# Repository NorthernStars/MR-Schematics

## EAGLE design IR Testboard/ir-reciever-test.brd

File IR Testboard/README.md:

IR-Testboard
============
Board to redirect IR data or/and serial Data.
Use jumpers on the board to redircet the RX or TX data to PC or an external logic.

Used for testing IR reciever.

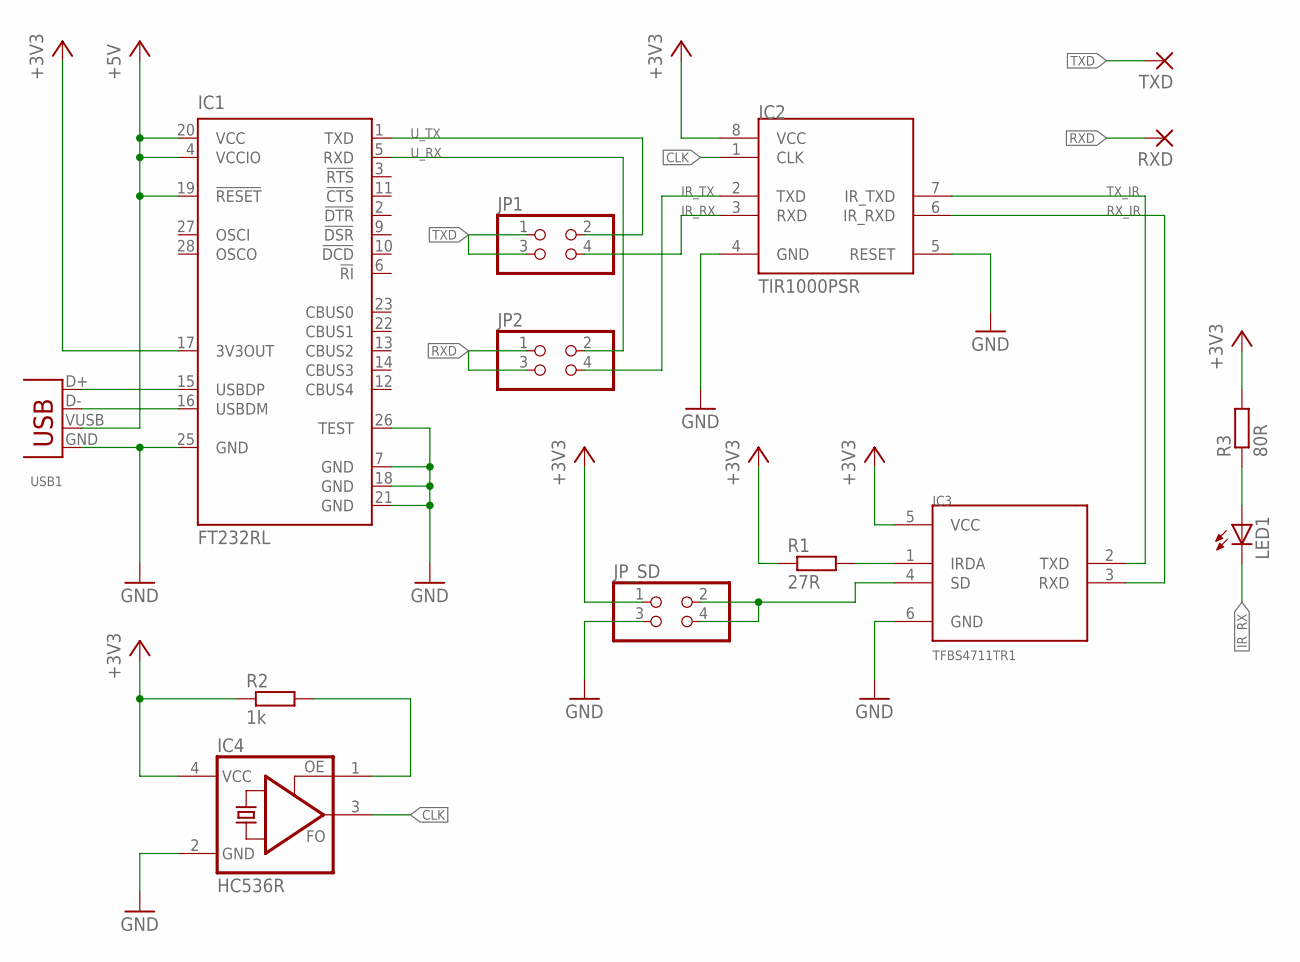
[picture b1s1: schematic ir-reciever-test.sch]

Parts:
IC1: FT232RL; SSOP28
IC2: TIR1000PSR; SO-08
IC3: TFBS4711TR1; TFBS4711
IC4: HC536R; HC536
JP1, JP2: PINHD-2X02_2.54-SMD; 2X02SMD
JP_SD: PINHD-2X02_2.54-SMD; 2X02SMD
LED1: LED3MM
R1: 27R; R1206
R2: 1k; R1206
R3: 80R; R1206
RXD: SMD5; SMD2,54-5,08
TXD: SMD5; SMD2,54-5,08
USB1: USB-B-S; USB-B-SMT

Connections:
+3V3: IC1.17 (3V3OUT), IC2.8 (VCC), IC3.5 (VCC), IC4.4 (VCC), JP_SD.1, R1.1, R2.1, R3.2
+5V: IC1.4 (VCCIO), IC1.19 (!RESET), IC1.20 (VCC), USB1.VUSB (VBUS)
CLK: IC2.1 (CLK), IC4.3 (FO)
D+: IC1.15 (USBDP), USB1.D+
D-: IC1.16 (USBDM), USB1.D-
GND: IC1.7 (GND), IC1.18 (GND), IC1.21 (GND), IC1.25 (GND), IC1.26 (TEST), IC2.4 (GND), IC2.5 (RESET), IC3.6 (GND), IC4.2 (GND), JP_SD.3, USB1.GND
IR_RX: IC2.3 (RXD), JP1.4, LED1.K (C)
IR_TX: IC2.2 (TXD), JP2.4
unnamed: LED1.A, R3.1
unnamed: IC3.1 (IRDA), R1.2
unnamed: IC3.4 (SD), JP_SD.2, JP_SD.4
unnamed: IC4.1 (OE), R2.2
RXD: JP2.1, JP2.3, RXD.1
RX_IR: IC2.6 (IR_RXD), IC3.3 (RXD)
TXD: JP1.1, JP1.3, TXD.1
TX_IR: IC2.7 (IR_TXD), IC3.2 (TXD)
U_RX: IC1.5 (RXD), JP2.2
U_TX: IC1.1 (TXD), JP1.2

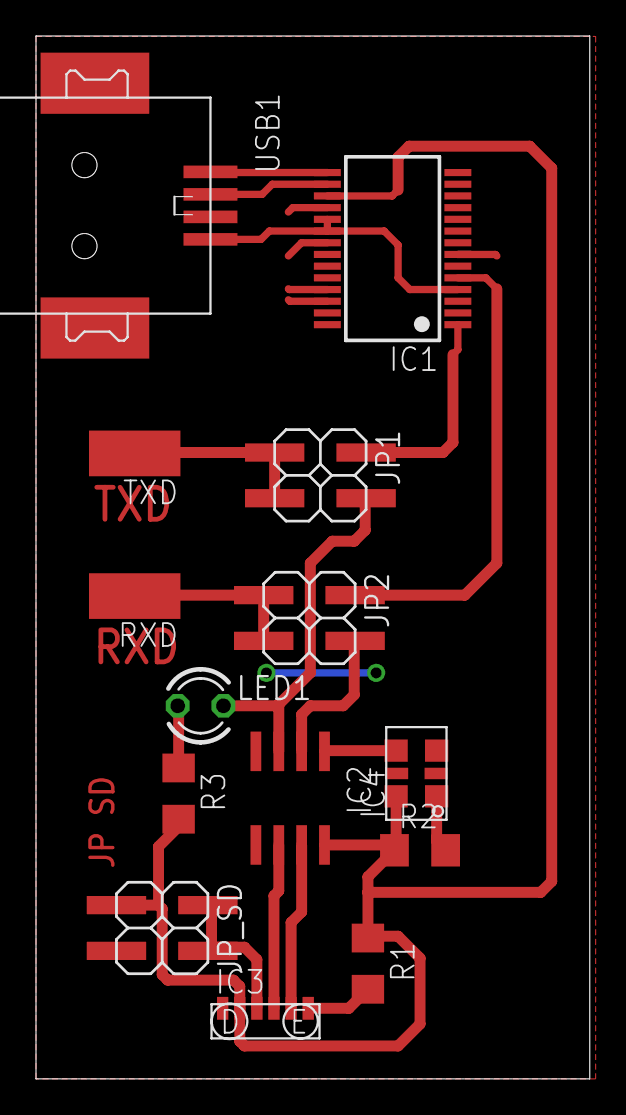
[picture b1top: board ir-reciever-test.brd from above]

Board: 2 copper layers, 30.8 x 57.9 mm, 14 parts (0 on the bottom side), 18 nets.

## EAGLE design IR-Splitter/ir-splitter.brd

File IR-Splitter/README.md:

IR-Splitter
===========
Hardware to split IR data load to seperate MOSFET channels.
Connect external power supply and IR data from IR-Transmitter to the board.
Voltage of power supply depends on you needs but test show that it should be between 5V and 12V (7.5V is recommended).

Connect IR-leds to the 10 IR-OUT pads. Try to balance the number of leds on the channels.
It's highly recommended to use a heatsink on the mosfets.

Test your installation with different intervals of load.
MOSFET's temperature should not be above 80°C!

It is possible to use this pcb as single layer board.

ATTENTION
---------
If you don't use our IR-Transmitter, take care that the IR-Splitter needs an inverted IR data input signal. So HIGH level is LOW and the other way round.

Also be aware that setting IR data input signal to LOW level will cause the leds to light up. This maybe damages them!

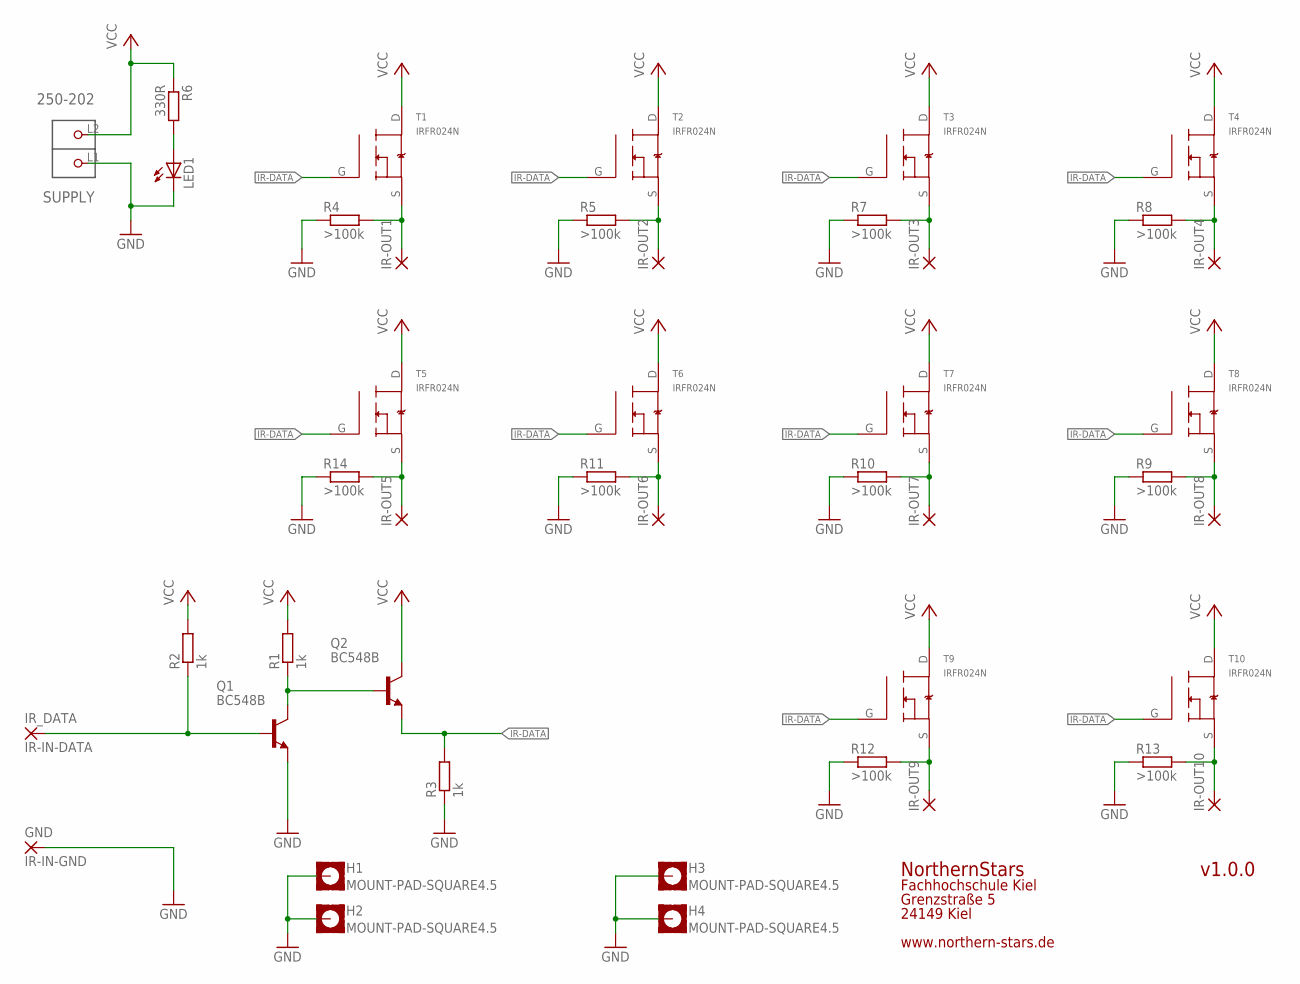
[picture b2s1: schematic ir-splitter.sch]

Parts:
GND: IR-IN-GND; 3,81/1,4
H1, H2, H3, H4: MOUNT-PAD-SQUARE4.5; 4,5-PAD-SQUARE
IR-OUT1, IR-OUT2, IR-OUT3, IR-OUT4, IR-OUT5, IR-OUT6, IR-OUT7, IR-OUT8, IR-OUT9, IR-OUT10: 3,81/1,4
IR_DATA: IR-IN-DATA; 3,81/1,4
LED1: LEDCHIPLED_1206; CHIPLED_1206
Q1, Q2: BC548B; TO92-EBC
R1, R2, R3: 1k; R1206
R4, R5, R7, R8, R9, R10, R11, R12, R13, R14: >100k; R1206
R6: 330R; R1206
SUPPLY: 250-202; P-250-202
T1, T2, T3, T4, T5, T6, T7, T8, T9, T10: IRFR024N; D-PAK

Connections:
GND: GND.1, H1.B4,5, H2.B4,5, H3.B4,5, H4.B4,5, LED1.C, Q1.E, R3.1, R4.1, R5.1, R7.1, R8.1, R9.1, R10.1, R11.1, R12.1, R13.1, R14.1, SUPPLY.L1 (P1)
IR-DATA: Q2.E, R3.2, T1.G, T2.G, T3.G, T4.G, T5.G, T6.G, T7.G, T8.G, T9.G, T10.G
unnamed: IR-OUT1.1, R4.2, T1.S
unnamed: IR-OUT2.1, R5.2, T2.S
unnamed: IR-OUT5.1, R14.2, T5.S
unnamed: IR-OUT6.1, R11.2, T6.S
unnamed: IR-OUT8.1, R9.2, T8.S
unnamed: IR-OUT7.1, R10.2, T7.S
unnamed: IR-OUT4.1, R8.2, T4.S
unnamed: IR-OUT3.1, R7.2, T3.S
unnamed: IR-OUT10.1, R13.2, T10.S
unnamed: IR-OUT9.1, R12.2, T9.S
unnamed: Q1.C, Q2.B, R1.1
unnamed: LED1.A, R6.2
unnamed: IR_DATA.1, Q1.B, R2.1
VCC: Q2.C, R1.2, R2.2, R6.1, SUPPLY.L2 (P2), T1.D, T2.D, T3.D, T4.D, T5.D, T6.D, T7.D, T8.D, T9.D, T10.D

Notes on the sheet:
NorthernStars
Fachhochschule Kiel
Grenzstraße 5
24149 Kiel
www.northern-stars.de
v1.0.0

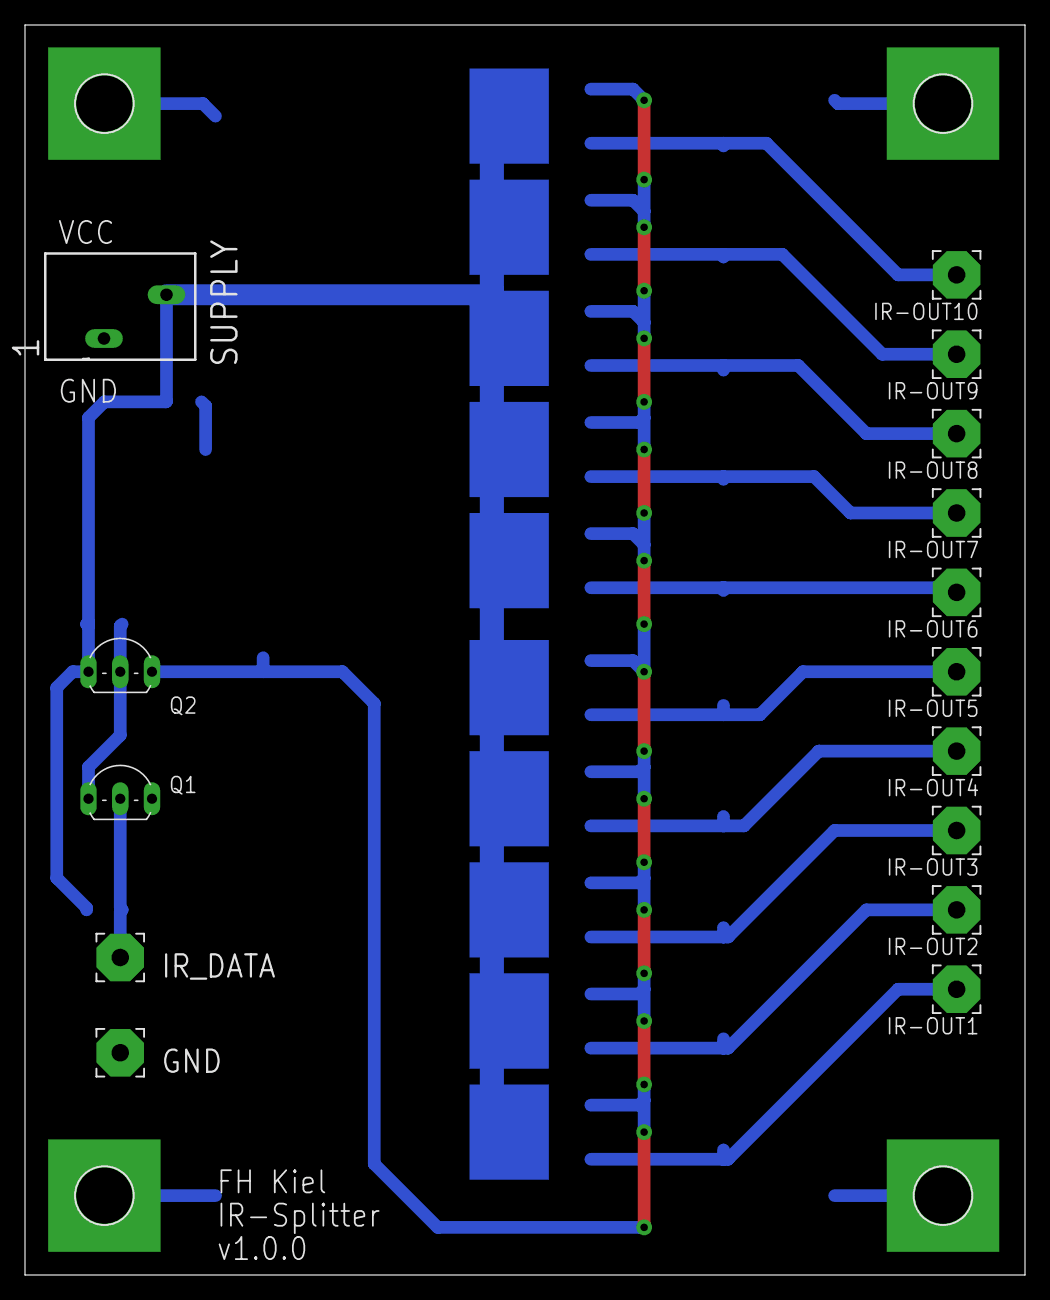
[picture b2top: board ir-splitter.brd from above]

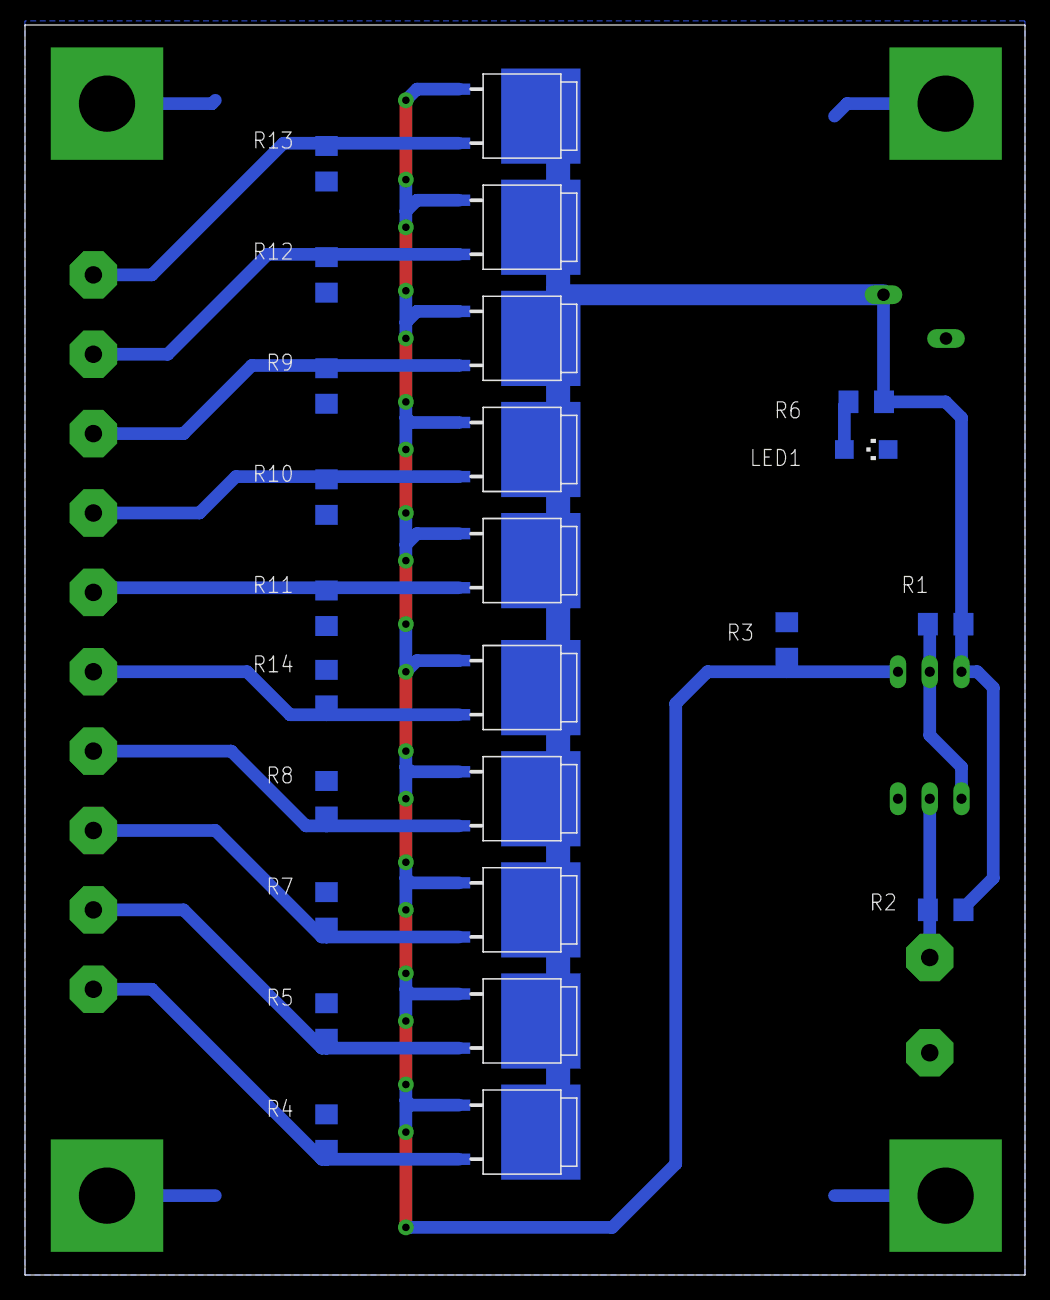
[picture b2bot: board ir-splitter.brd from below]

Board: 2 copper layers, 80.0 x 100.0 mm, 44 parts (25 on the bottom side), 16 nets.

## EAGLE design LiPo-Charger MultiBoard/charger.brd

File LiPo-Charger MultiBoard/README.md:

LiPo-Charger MultiBoard
=======================
This charger consists of several small 50x50mm board that can get connected to each other to build a charger station of your preferred size.
* The charger board includes charging circuits for charging two LiPo batteries with ~200mA/battery.
* The supply board is for connecting the charger boards to a 5V power suplly. Maximum output current ist 5.0A. It's recommended to use max. 10 charger boards at one supply board.

Order online
------------
The pcbs can be ordered very cheap from www.dirtypcbs.com
* Charger: http://dirtypcbs.com/view.php?share=21687&accesskey=b3ce18c981010ed7b3aafff49d6ba531
* Supply: http://dirtypcbs.com/view.php?share=3158&accesskey=d8e7d692d385bc674d54f8e41f2b1a86

The electronic parts should get ordered from Farnell (http://www.farnell.com) and Reichelt (https://secure.reichelt.de/index.html?LANGUAGE=EN).

The LibreOffice calculation Parts-Calculation.ods includes an adjustable list of parts to oder.

Usage
-----
To use the charger, connect at least one charger board to the supply board.
Connect the supply board with your 5V power supply. Attention: There is no protection circuit for higher voltages!
You can connect other chargers to the other sides of any charger already connected to the supply board or to the supply board itself.

I²C / TWI Bus
-------
The charger boards include a I²C (or TWI) interface to connect a microcontroller or any other logic to the robots.
For that the charger board stops the robot (depending on the correct firmware) from booting. After that you can access the robot internal hardware via I²C bus.

There will be an additional board to manage the robots in the future.

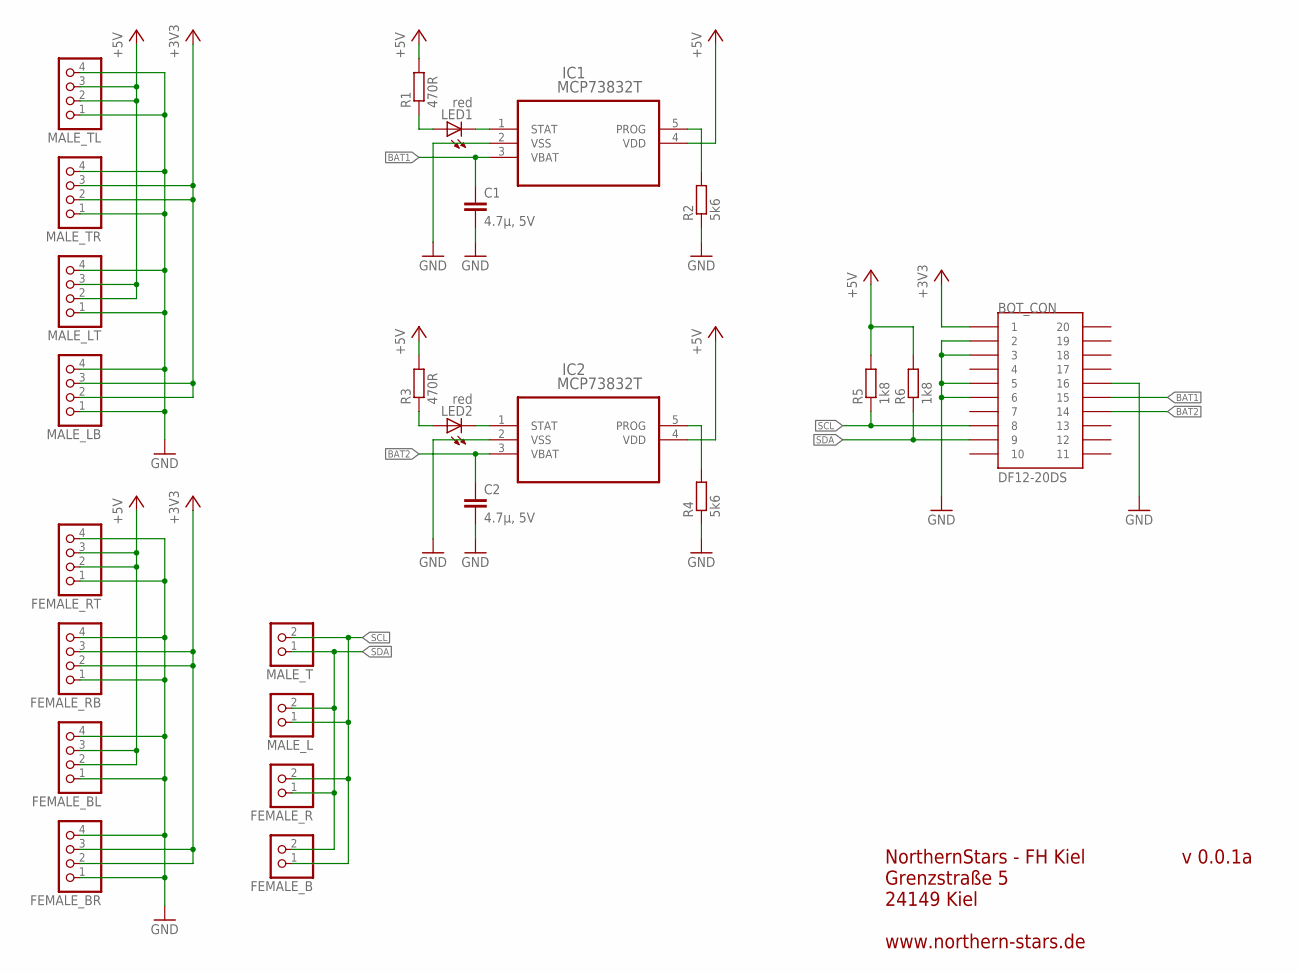
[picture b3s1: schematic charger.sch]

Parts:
BOT_CON: DF12-20DS
C1, C2: 4.7µ, 5V; C1206
FEMALE_B: PINHD-1X02_2.54-90°; 1X02/90
FEMALE_BL: PINHD-1X04_2.54-90°; 1X04/90
FEMALE_BR: PINHD-1X04_2.54-90°; 1X04/90
FEMALE_R: PINHD-1X02_2.54-90°; 1X02/90
FEMALE_RB: PINHD-1X04_2.54-90°; 1X04/90
FEMALE_RT: PINHD-1X04_2.54-90°; 1X04/90
IC1, IC2: MCP73832T; SOT95P300X145-5N
LED1, LED2: red; CHIPLED_1206
MALE_L: PINHD-1X02_2.54-90°; 1X02/90
MALE_LB: PINHD-1X04_2.54-90°; 1X04/90
MALE_LT: PINHD-1X04_2.54-90°; 1X04/90
MALE_T: PINHD-1X02_2.54-90°; 1X02/90
MALE_TL: PINHD-1X04_2.54-90°; 1X04/90
MALE_TR: PINHD-1X04_2.54-90°; 1X04/90
R1, R3: 470R; R1206
R2, R4: 5k6; R1206
R5, R6: 1k8; R1206

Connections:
+3V3: BOT_CON.1, FEMALE_BR.2, FEMALE_BR.3, FEMALE_RB.2, FEMALE_RB.3, MALE_LB.2, MALE_LB.3, MALE_TR.2, MALE_TR.3
+5V: FEMALE_BL.2, FEMALE_BL.3, FEMALE_RT.2, FEMALE_RT.3, IC1.4 (VDD), IC2.4 (VDD), MALE_LT.2, MALE_LT.3, MALE_TL.2, MALE_TL.3, R1.2, R3.2, R5.2, R6.2
BAT1: BOT_CON.15, C1.1, IC1.3 (VBAT)
BAT2: BOT_CON.14, C2.1, IC2.3 (VBAT)
GND: BOT_CON.2, BOT_CON.3, BOT_CON.5, BOT_CON.6, BOT_CON.16, C1.2, C2.2, FEMALE_BL.1, FEMALE_BL.4, FEMALE_BR.1, FEMALE_BR.4, FEMALE_RB.1, FEMALE_RB.4, FEMALE_RT.1, FEMALE_RT.4, IC1.2 (VSS), IC2.2 (VSS), MALE_LB.1, MALE_LB.4, MALE_LT.1, MALE_LT.4, MALE_TL.1, MALE_TL.4, MALE_TR.1, MALE_TR.4, R2.1, R4.1
unnamed: IC1.1 (STAT), LED1.C
unnamed: LED1.A, R1.1
unnamed: IC2.1 (STAT), LED2.C
unnamed: IC1.5 (PROG), R2.2
unnamed: LED2.A, R3.1
unnamed: IC2.5 (PROG), R4.2
SCL: BOT_CON.8, FEMALE_B.1, FEMALE_R.2, MALE_L.1, MALE_T.2, R5.1
SDA: BOT_CON.9, FEMALE_B.2, FEMALE_R.1, MALE_L.2, MALE_T.1, R6.1

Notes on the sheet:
v 0.0.1a
NorthernStars - FH Kiel Grenzstraße 5 24149 Kiel www.northern-stars.de

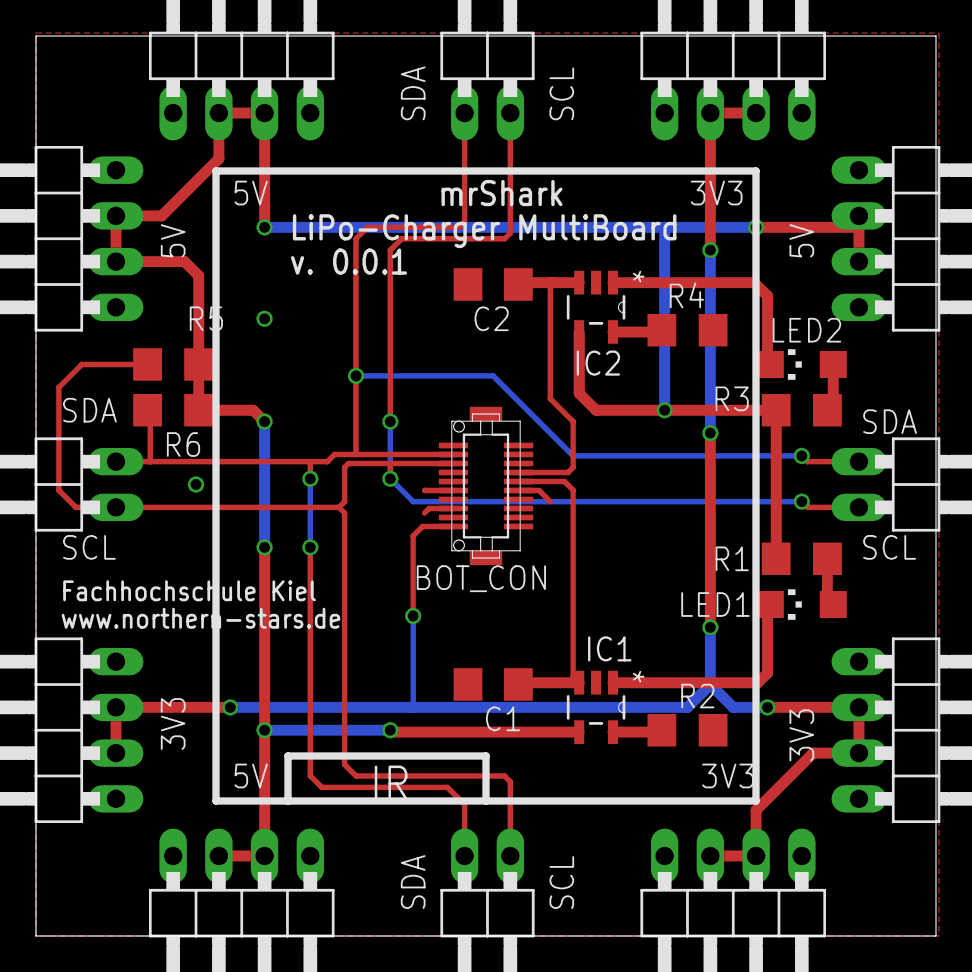
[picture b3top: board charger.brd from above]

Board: 2 copper layers, 50.0 x 50.0 mm, 25 parts (0 on the bottom side), 13 nets.

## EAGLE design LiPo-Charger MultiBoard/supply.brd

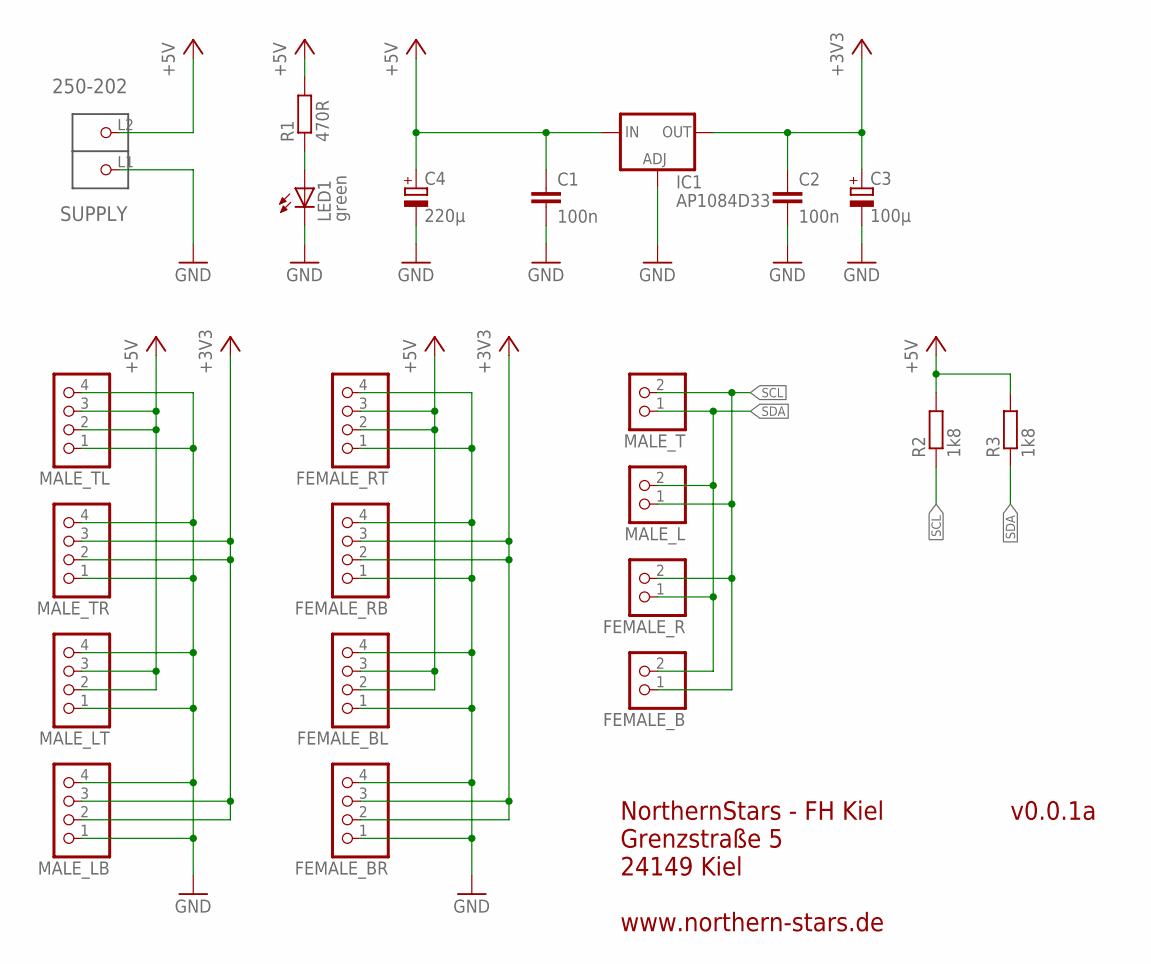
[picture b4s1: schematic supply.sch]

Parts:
C1, C2: 100n; C1206
C3: 100µ; UD-6,3X5,8_NICHICON
C4: 220µ; UD-6,3X7,7_NICHICON
FEMALE_B: PINHD-1X02_2.54-90°; 1X02/90
FEMALE_BL: PINHD-1X04_2.54-90°; 1X04/90
FEMALE_BR: PINHD-1X04_2.54-90°; 1X04/90
FEMALE_R: PINHD-1X02_2.54-90°; 1X02/90
FEMALE_RB: PINHD-1X04_2.54-90°; 1X04/90
FEMALE_RT: PINHD-1X04_2.54-90°; 1X04/90
IC1: AP1084D33; TO252
LED1: green; CHIPLED_1206
MALE_L: PINHD-1X02_2.54-90°; 1X02/90
MALE_LB: PINHD-1X04_2.54-90°; 1X04/90
MALE_LT: PINHD-1X04_2.54-90°; 1X04/90
MALE_T: PINHD-1X02_2.54-90°; 1X02/90
MALE_TL: PINHD-1X04_2.54-90°; 1X04/90
MALE_TR: PINHD-1X04_2.54-90°; 1X04/90
R1: 470R; R1206
R2, R3: 1k8; R1206
SUPPLY: 250-202; P-250-202

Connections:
+3V3: C2.1, C3.+, FEMALE_BR.2, FEMALE_BR.3, FEMALE_RB.2, FEMALE_RB.3, IC1.3 (OUT), MALE_LB.2, MALE_LB.3, MALE_TR.2, MALE_TR.3
+5V: C1.1, C4.+, FEMALE_BL.2, FEMALE_BL.3, FEMALE_RT.2, FEMALE_RT.3, IC1.2 (IN), MALE_LT.2, MALE_LT.3, MALE_TL.2, MALE_TL.3, R1.2, R2.2, R3.2, SUPPLY.L2 (P2)
GND: C1.2, C2.2, C3.-, C4.-, FEMALE_BL.1, FEMALE_BL.4, FEMALE_BR.1, FEMALE_BR.4, FEMALE_RB.1, FEMALE_RB.4, FEMALE_RT.1, FEMALE_RT.4, IC1.1 (ADJ), LED1.C, MALE_LB.1, MALE_LB.4, MALE_LT.1, MALE_LT.4, MALE_TL.1, MALE_TL.4, MALE_TR.1, MALE_TR.4, SUPPLY.L1 (P1)
unnamed: LED1.A, R1.1
SCL: FEMALE_B.1, FEMALE_R.2, MALE_L.1, MALE_T.2, R2.1
SDA: FEMALE_B.2, FEMALE_R.1, MALE_L.2, MALE_T.1, R3.1

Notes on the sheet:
v0.0.1a
NorthernStars - FH Kiel Grenzstraße 5 24149 Kiel www.northern-stars.de

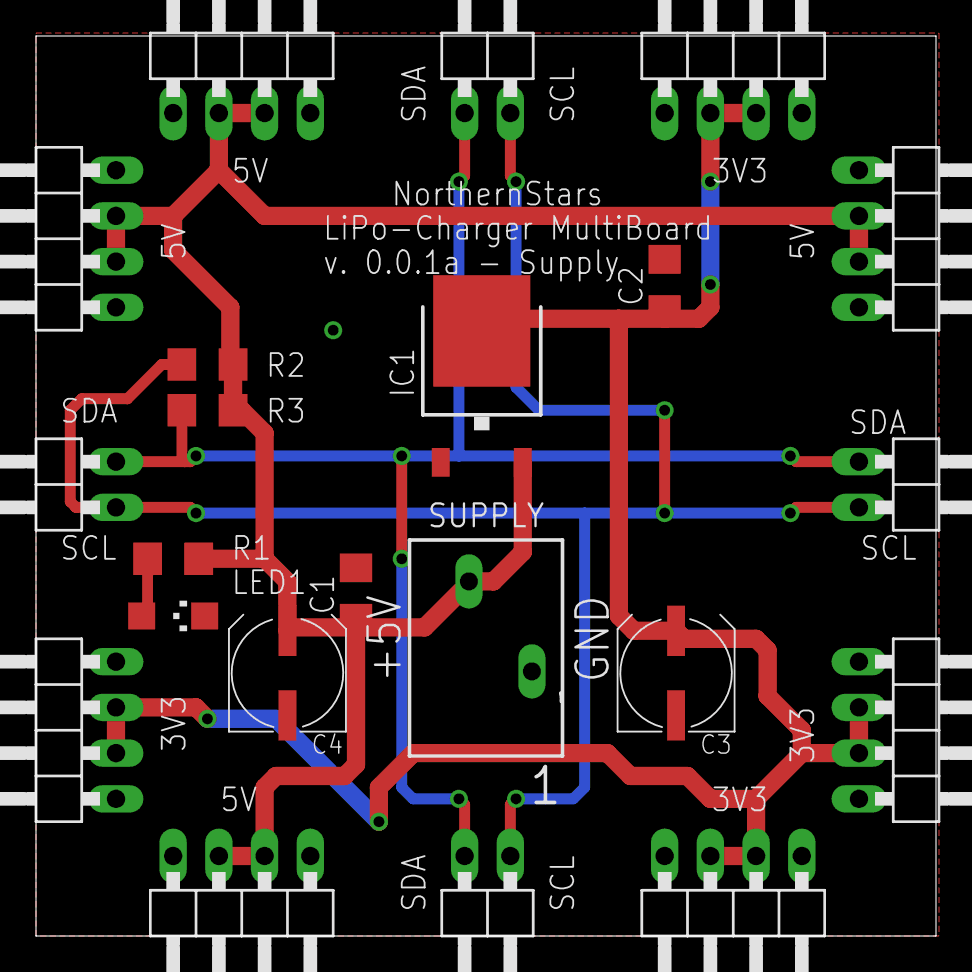
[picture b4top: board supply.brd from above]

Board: 2 copper layers, 50.0 x 50.0 mm, 22 parts (0 on the bottom side), 6 nets.

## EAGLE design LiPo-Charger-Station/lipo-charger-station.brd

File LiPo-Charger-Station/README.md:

LiPo-Charger-Station
====================

## DO NOT USE, NOT TESTED AND LAYOUT OUTDATED

This charger station includes LiPo charger circuits to charge 9 robots with 2 LiPo batterys each.
Each battery will be charged with ~500mA. The station includes a microcontroller to access the robots internal hardware.

This project currently not maintained and includes some erros. Use LiPo-Charger MutliBoard instead.

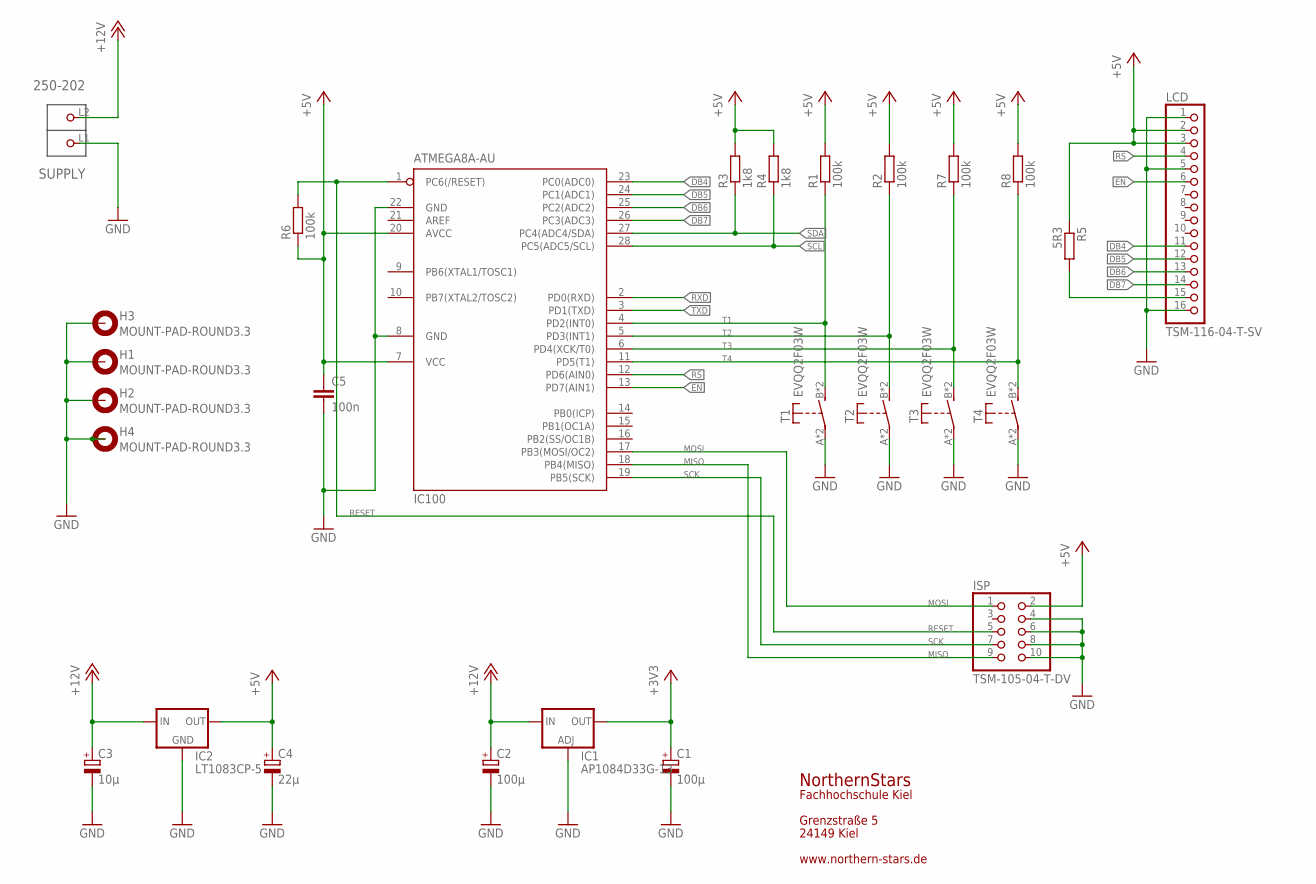
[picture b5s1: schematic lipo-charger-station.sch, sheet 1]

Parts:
C1, C2: 100µ; PANASONIC_G
C3: 10µ; PANASONIC_D
C4: 22µ; PANASONIC_E
C5: 100n; C1206
H1, H2, H3, H4: MOUNT-PAD-ROUND3.3; 3,3-PAD
IC1: AP1084D33G-13; TO252
IC2: LT1083CP-5; TO3P
IC100: ATMEGA8A-AU; DIL28-3
ISP: TSM-105-04-T-DV; 2X05SMD
LCD: TSM-116-04-T-SV; 1X16SMD
R1, R2, R6, R7, R8: 100k; R1206
R3, R4: 1k8; R1206
R5: 5R3; R1206
SUPPLY: 250-202; P-250-202
T1, T2, T3, T4: EVQQ2F03W; SMD_TASTER_PANASONIC

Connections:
+3V3: C1.+, IC1.3 (OUT); also elsewhere on the board
+5V: C4.+, C5.1, IC2.2 (OUT), IC100.7 (VCC), IC100.20 (AVCC), ISP.2, LCD.2, LCD.3, R1.2, R2.2, R3.2, R4.2, R5.1, R6.1, R7.2, R8.2; also elsewhere on the board
+12V: C2.+, C3.+, IC1.2 (IN), IC2.3 (IN), SUPPLY.L2 (P2)
DB4: IC100.23 (PC0(ADC0)), LCD.11
DB5: IC100.24 (PC1(ADC1)), LCD.12
DB6: IC100.25 (PC2(ADC2)), LCD.13
DB7: IC100.26 (PC3(ADC3)), LCD.14
EN: IC100.13 (PD7(AIN1)), LCD.6
GND: C1.-, C2.-, C3.-, C4.-, C5.2, H1.B3,3, H2.B3,3, H3.B3,3, H4.B3,3, IC1.1 (ADJ), IC2.1 (GND), IC100.8 (GND), IC100.22 (GND), ISP.4, ISP.6, ISP.8, ISP.10, LCD.1, LCD.5, LCD.16, SUPPLY.L1 (P1), T1.A, T1.A', T2.A, T2.A', T3.A, T3.A', T4.A, T4.A'; also elsewhere on the board
LEDA: LCD.15, R5.2
MISO: IC100.18 (PB4(MISO)), ISP.9
MOSI: IC100.17 (PB3(MOSI/OC2)), ISP.1
RESET: IC100.1 (PC6(/RESET)), ISP.5, R6.2
RS: IC100.12 (PD6(AIN0)), LCD.4
RXD: IC100.2 (PD0(RXD))
SCK: IC100.19 (PB5(SCK)), ISP.7
SCL: IC100.28 (PC5(ADC5/SCL)), R4.1; also elsewhere on the board
SDA: IC100.27 (PC4(ADC4/SDA)), R3.1; also elsewhere on the board
T1: IC100.4 (PD2(INT0)), R1.1, T1.B (S), T1.B' (S)
T2: IC100.5 (PD3(INT1)), R2.1, T2.B (S), T2.B' (S)
T3: IC100.6 (PD4(XCK/T0)), R7.1, T3.B (S), T3.B' (S)
T4: IC100.11 (PD5(T1)), R8.1, T4.B (S), T4.B' (S)
TXD: IC100.3 (PD1(TXD))

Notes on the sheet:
NorthernStars
Fachhochschule Kiel
Grenzstraße 5
24149 Kiel
www.northern-stars.de

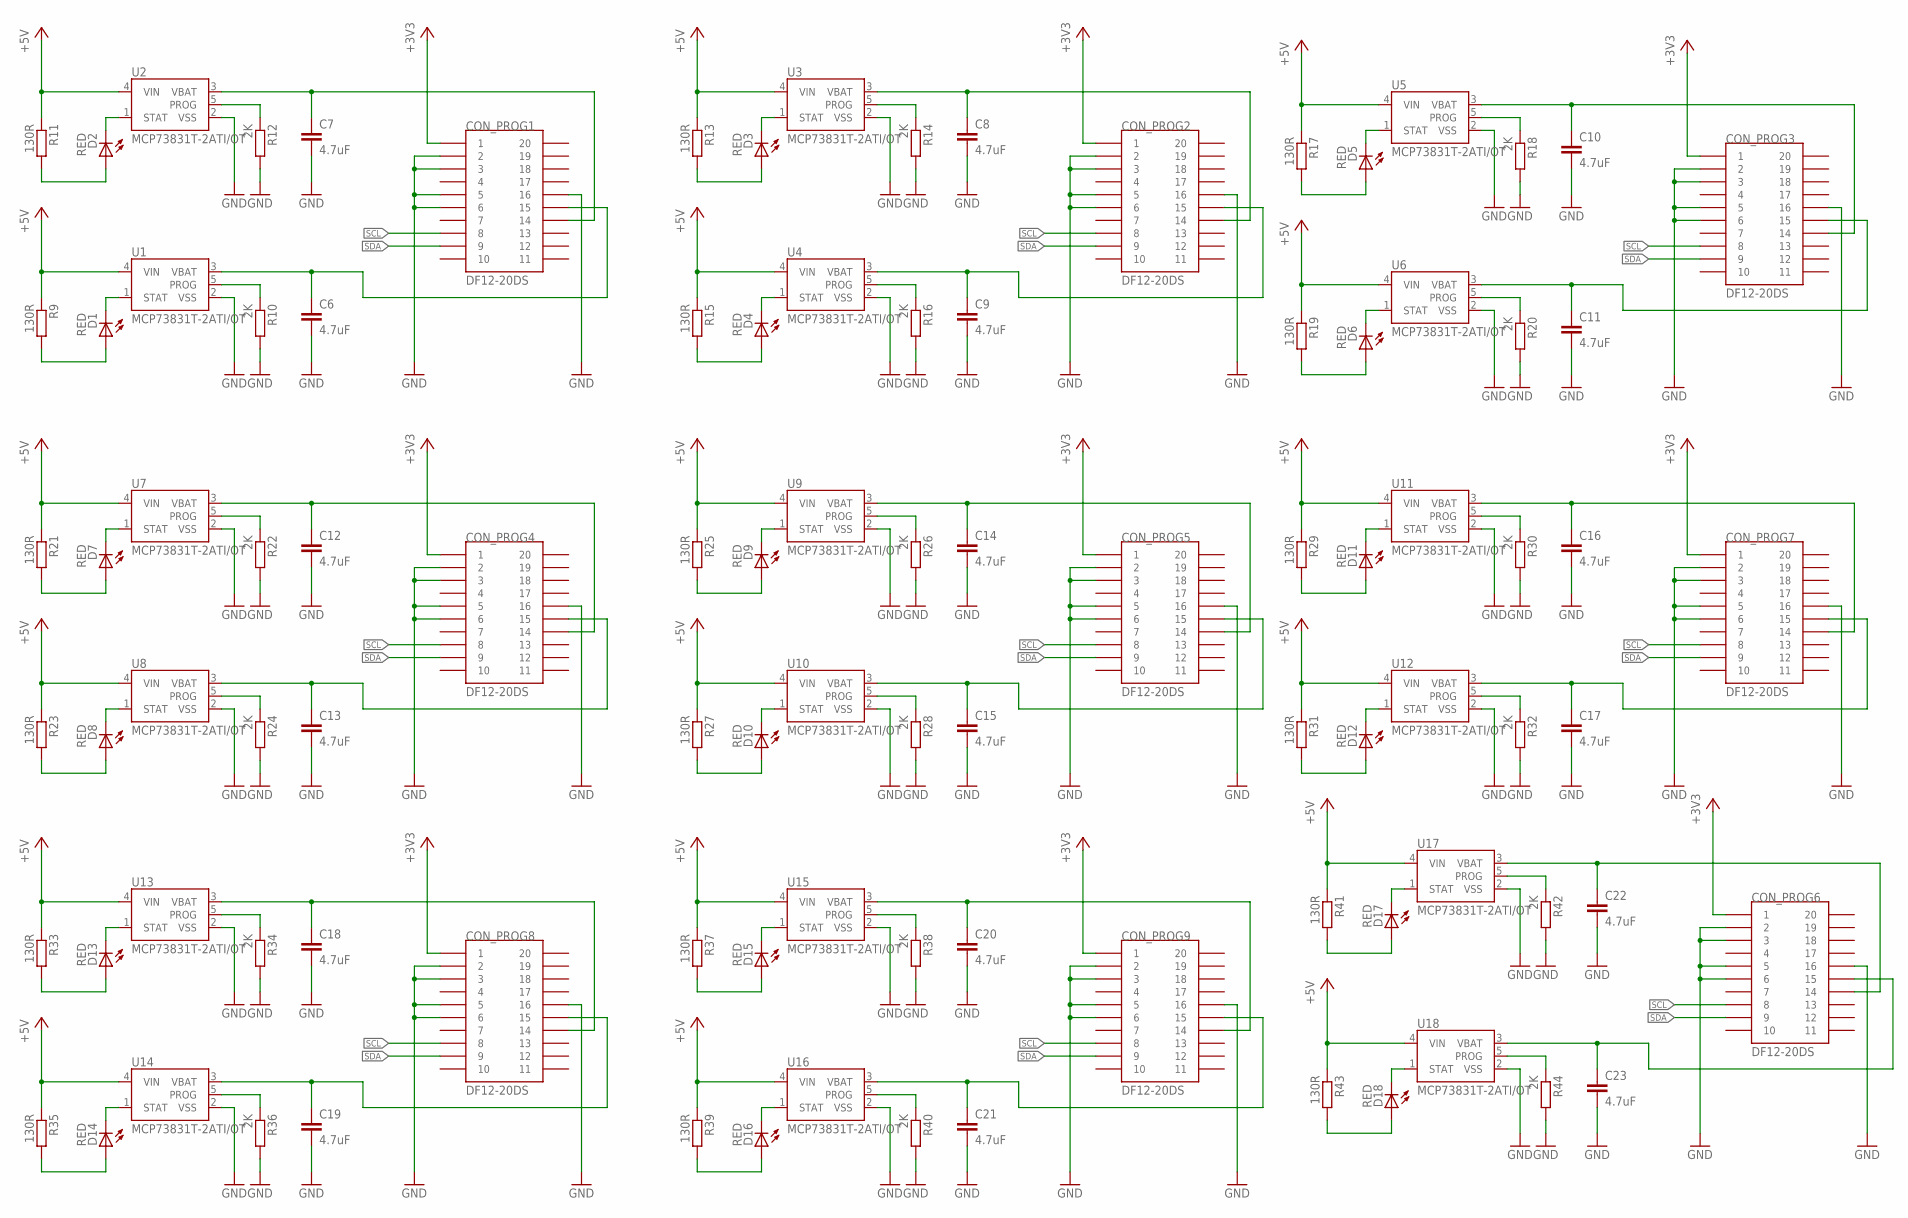
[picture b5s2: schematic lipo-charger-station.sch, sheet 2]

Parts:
C6, C7, C8, C9, C10, C11, C12, C13, C14, C15, C16, C17, C18, C19, C20, C21, C22, C23: 4.7uF; C1206
CON_PROG1, CON_PROG2, CON_PROG3, CON_PROG4, CON_PROG5, CON_PROG6, CON_PROG7, CON_PROG8, CON_PROG9: DF12-20DS
D1, D2, D3, D4, D5, D6, D7, D8, D9, D10, D11, D12, D13, D14, D15, D16, D17, D18: RED; CHIPLED_1206
R9, R11, R13, R15, R17, R19, R21, R23, R25, R27, R29, R31, R33, R35, R37, R39, R41, R43: 130R; R1206
R10, R12, R14, R16, R18, R20, R22, R24, R26, R28, R30, R32, R34, R36, R38, R40, R42, R44: 2K; R1206
U1, U2, U3, U4, U5, U6, U7, U8, U9, U10, U11, U12, U13, U14, U15, U16, U17, U18: MCP73831T-2ATI/OT; SOT23-5

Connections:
+3V3: CON_PROG1.1, CON_PROG2.1, CON_PROG3.1, CON_PROG4.1, CON_PROG5.1, CON_PROG6.1, CON_PROG7.1, CON_PROG8.1, CON_PROG9.1; also elsewhere on the board
+5V: R9.1, R11.1, R13.1, R15.1, R17.1, R19.1, R21.1, R23.1, R25.1, R27.1, R29.1, R31.1, R33.1, R35.1, R37.1, R39.1, R41.1, R43.1, U1.4 (VIN), U2.4 (VIN), U3.4 (VIN), U4.4 (VIN), U5.4 (VIN), U6.4 (VIN), U7.4 (VIN), U8.4 (VIN), U9.4 (VIN), U10.4 (VIN), U11.4 (VIN), U12.4 (VIN), U13.4 (VIN), U14.4 (VIN), U15.4 (VIN), U16.4 (VIN), U17.4 (VIN), U18.4 (VIN); also elsewhere on the board
B1_BAT1+: C7.1, CON_PROG1.14, U2.3 (VBAT)
B1_BAT1+1: C8.1, CON_PROG2.14, U3.3 (VBAT)
B1_BAT1+3: C10.1, CON_PROG3.14, U5.3 (VBAT)
B1_BAT1+4: C12.1, CON_PROG4.14, U7.3 (VBAT)
B1_BAT1+5: C16.1, CON_PROG7.14, U11.3 (VBAT)
B1_BAT1+6: C14.1, CON_PROG5.14, U9.3 (VBAT)
B1_BAT1+7: C22.1, CON_PROG6.14, U17.3 (VBAT)
B1_BAT1+9: C18.1, CON_PROG8.14, U13.3 (VBAT)
B1_BAT1+10: C20.1, CON_PROG9.14, U15.3 (VBAT)
B1_BAT2+: C6.1, CON_PROG1.15, U1.3 (VBAT)
B1_BAT2+1: C9.1, CON_PROG2.15, U4.3 (VBAT)
B1_BAT2+2: C11.1, CON_PROG3.15, U6.3 (VBAT)
B1_BAT2+3: C13.1, CON_PROG4.15, U8.3 (VBAT)
B1_BAT2+4: C15.1, CON_PROG5.15, U10.3 (VBAT)
B1_BAT2+5: C17.1, CON_PROG7.15, U12.3 (VBAT)
B1_BAT2+6: C19.1, CON_PROG8.15, U14.3 (VBAT)
B1_BAT2+7: C21.1, CON_PROG9.15, U16.3 (VBAT)
B1_BAT2+8: C23.1, CON_PROG6.15, U18.3 (VBAT)
GND: C6.2, C7.2, C8.2, C9.2, C10.2, C11.2, C12.2, C13.2, C14.2, C15.2, C16.2, C17.2, C18.2, C19.2, C20.2, C21.2, C22.2, C23.2, CON_PROG1.2, CON_PROG1.3, CON_PROG1.5, CON_PROG1.6, CON_PROG1.16, CON_PROG2.2, CON_PROG2.3, CON_PROG2.5, CON_PROG2.6, CON_PROG2.16, CON_PROG3.2, CON_PROG3.3, CON_PROG3.5, CON_PROG3.6, CON_PROG3.16, CON_PROG4.2, CON_PROG4.3, CON_PROG4.5, CON_PROG4.6, CON_PROG4.16, CON_PROG5.2, CON_PROG5.3, CON_PROG5.5, CON_PROG5.6, CON_PROG5.16, CON_PROG6.2, CON_PROG6.3, CON_PROG6.5, CON_PROG6.6, CON_PROG6.16, CON_PROG7.2, CON_PROG7.3, CON_PROG7.5, CON_PROG7.6, CON_PROG7.16, CON_PROG8.2, CON_PROG8.3, CON_PROG8.5, CON_PROG8.6, CON_PROG8.16, CON_PROG9.2, CON_PROG9.3, CON_PROG9.5, CON_PROG9.6, CON_PROG9.16, R10.2, R12.2, R14.2, R16.2, R18.2, R20.2, R22.2, R24.2, R26.2, R28.2, R30.2, R32.2, R34.2, R36.2, R38.2, R40.2, R42.2, R44.2, U1.2 (VSS), U2.2 (VSS), U3.2 (VSS), U4.2 (VSS), U5.2 (VSS), U6.2 (VSS), U7.2 (VSS), U8.2 (VSS), U9.2 (VSS), U10.2 (VSS), U11.2 (VSS), U12.2 (VSS), U13.2 (VSS), U14.2 (VSS), U15.2 (VSS), U16.2 (VSS), U17.2 (VSS), U18.2 (VSS); also elsewhere on the board
unnamed: D2.A, R11.2
unnamed: D1.A, R9.2
unnamed: D3.A, R13.2
unnamed: D4.A, R15.2
unnamed: D5.A, R17.2
unnamed: D6.A, R19.2
unnamed: D7.A, R21.2
unnamed: D8.A, R23.2
unnamed: D9.A, R25.2
unnamed: D10.A, R27.2
unnamed: D11.A, R29.2
unnamed: D12.A, R31.2
unnamed: D13.A, R33.2
unnamed: D14.A, R35.2
unnamed: D15.A, R37.2
unnamed: D16.A, R39.2
unnamed: D17.A, R41.2
unnamed: D18.A, R43.2
PROG: R12.1, U2.5 (PROG)
PROG1: R10.1, U1.5 (PROG)
PROG2: R14.1, U3.5 (PROG)
PROG3: R16.1, U4.5 (PROG)
PROG4: R18.1, U5.5 (PROG)
PROG5: R20.1, U6.5 (PROG)
PROG6: R22.1, U7.5 (PROG)
PROG7: R24.1, U8.5 (PROG)
PROG8: R26.1, U9.5 (PROG)
PROG9: R28.1, U10.5 (PROG)
PROG10: R30.1, U11.5 (PROG)
PROG11: R32.1, U12.5 (PROG)
PROG12: R34.1, U13.5 (PROG)
PROG13: R36.1, U14.5 (PROG)
PROG14: R38.1, U15.5 (PROG)
PROG15: R40.1, U16.5 (PROG)
PROG16: R42.1, U17.5 (PROG)
PROG17: R44.1, U18.5 (PROG)
SCL: CON_PROG1.8, CON_PROG2.8, CON_PROG3.8, CON_PROG4.8, CON_PROG5.8, CON_PROG6.8, CON_PROG7.8, CON_PROG8.8, CON_PROG9.8; also elsewhere on the board
SDA: CON_PROG1.9, CON_PROG2.9, CON_PROG3.9, CON_PROG4.9, CON_PROG5.9, CON_PROG6.9, CON_PROG7.9, CON_PROG8.9, CON_PROG9.9; also elsewhere on the board
STAT: D2.C, U2.1 (STAT)
STAT1: D1.C, U1.1 (STAT)
STAT2: D3.C, U3.1 (STAT)
STAT3: D4.C, U4.1 (STAT)
STAT4: D5.C, U5.1 (STAT)
STAT5: D6.C, U6.1 (STAT)
STAT6: D7.C, U7.1 (STAT)
STAT7: D8.C, U8.1 (STAT)
STAT8: D9.C, U9.1 (STAT)
STAT9: D10.C, U10.1 (STAT)
STAT10: D11.C, U11.1 (STAT)
STAT11: D12.C, U12.1 (STAT)
STAT12: D13.C, U13.1 (STAT)
STAT13: D14.C, U14.1 (STAT)
STAT14: D15.C, U15.1 (STAT)
STAT15: D16.C, U16.1 (STAT)
STAT16: D17.C, U17.1 (STAT)
STAT17: D18.C, U18.1 (STAT)
